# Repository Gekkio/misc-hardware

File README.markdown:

# Miscellaneous/utility/convenience hardware by Gekkio
Licensed under Creative Commons Attribution 4.0 International.

Used libraries:

* [gekkio-kicad-libs](https://github.com/Gekkio/gekkio-kicad-libs)
* [kicad-footprints](https://github.com/KiCad/kicad-footprints)
* [kicad-symbols](https://github.com/KiCad/kicad-symbols)

## ARM-JTAG-TC2050-AVR

Adapts 20-pin (2x10) 2.54 inch ARM JTAG to 10-pin IDC connector using AVR JTAG
pinout (compatible with Tag-Connect TC2050).

* PCB size: 37x51mm
* PCB thickness: any
* Layer count: 2
* Surface finish: any

## BRK-QFP-32-7x7-P0.8

Breakout board for one QFP-32 component (7x7mm body, pitch 0.8mm).

* PCB size: 39.6x52.5mm
* PCB thickness: any (1.0mm recommended)
* Layer count: 2
* Surface finish: any (ENIG recommended)

## BRK-QFP-44-10x10-P0.8

Breakout board for one QFP-44 component (10x10mm body, pitch 0.8mm).

* PCB size: 39.6x52.5mm
* PCB thickness: any (1.0mm recommended)
* Layer count: 2
* Surface finish: any (ENIG recommended)

## BRK-QFP-44-10x10-P0.8-Sharp

Breakout board for one QFP-44 component (10x10mm body, pitch 0.8mm, different
footprint used by Sharp Corporation).

* PCB size: 39.6x52.5mm
* PCB thickness: any (1.0mm recommended)
* Layer count: 2
* Surface finish: any (ENIG recommended)

## BRK-QFP-56-10x10-P0.65

Breakout board for one QFP-56 component (10x10mm body, pitch 0.65mm).

* PCB size: 45.6x57.3mm
* PCB thickness: any (1.0mm recommended)
* Layer count: 2
* Surface finish: any (ENIG recommended)

## BRK-SOT-23-3

Breakout board for two SOT-23-3 components.

* PCB size: 16.3x23.4mm
* PCB thickness: any (1.0mm recommended)
* Layer count: 2
* Surface finish: any (ENIG recommended)

## BRK-SSOP-16-4.4x5.2-P0.65

Breakout board for one SSOP-16 component (4.4x5.2mm body, pitch 0.65mm).

* PCB size: 24x32.7mm
* PCB thickness: any (1.0mm recommended)
* Layer count: 2
* Surface finish: any (ENIG recommended)

## BRK-SSOP-18-6x7.4-P0.8

Breakout board for one SSOP-18 component (6x7.4mm body, pitch 0.8mm).

* PCB size: 24x35.3mm
* PCB thickness: any (1.0mm recommended)
* Layer count: 2
* Surface finish: any (ENIG recommended)

## BRK-TSSOP-14-4.4x5-P0.65

Breakout board for one TSSOP-14 component (4.4x5mm body, pitch 0.65mm).

* PCB size: 18.9x30.2mm
* PCB thickness: any (1.0mm recommended)
* Layer count: 2
* Surface finish: any (ENIG recommended)

## BRK-TSSOP-20-4.4x6.5-P0.65

Breakout board for one TSSOP-20 component (4.4x6.5mm body, pitch 0.65mm).

* PCB size: 18.9x37.8mm
* PCB thickness: any (1.0mm recommended)
* Layer count: 2
* Surface finish: any (ENIG recommended)

## BRK-TSSOP-24-4.4x7.8-P0.65

Breakout board for one TSSOP-24 component (4.4x7.8mm body, pitch 0.65mm).

* PCB size: 18.9x42.9mm
* PCB thickness: any (1.0mm recommended)
* Layer count: 2
* Surface finish: any (ENIG recommended)

## BRK-VSSOP-8-2.4x2.1-P0.5

Breakout board for one VSSOP-8 component (2.4x2.1mm body, pitch 0.5mm).

* PCB size: 16.3x22.6mm
* PCB thickness: any (1.0mm recommended)
* Layer count: 2
* Surface finish: any (ENIG recommended)

## EV-BA33Dxx

Evaluation/breakout board for Rohm BA33Dxx linear regulators.

* PCB size: 20x29mm
* PCB thickness: any
* Layer count: 2
* Surface finish: any (ENIG recommended)

## EV-MAX-V-E64

Evaluation/breakout board for MAX V CPLDs in EQFP-64 package.

* PCB size: 70x70mm
* PCB thickness: any
* Layer count: 2
* Surface finish: any (ENIG recommended)

## PIC-ICSP-504050

Adapts 6-pin (1x6) PIC ICSP to 5-pin Molex 504050 connector.

* PCB size: 30x40mm
* PCB thickness: any
* Layer count: 2
* Surface finish: any (ENIG recommended)

## PIC-ICSP-TC2030

Adapts 6-pin (1x6) PIC ICSP to 6-pin IDC connector (compatible with Tag-Connect
TC2030).

* PCB size: 25x35mm
* PCB thickness: any
* Layer count: 2
* Surface finish: any

## TC2050-OOPS

Did you use Counter_Clockwise footprint instead of Odd_Even for TC2050 in some design? Oops!
This board fixes the pinout in this kind of scenario.

* PCB size: 27x25mm
* PCB thickness: any
* Layer count: 2
* Surface finish: any

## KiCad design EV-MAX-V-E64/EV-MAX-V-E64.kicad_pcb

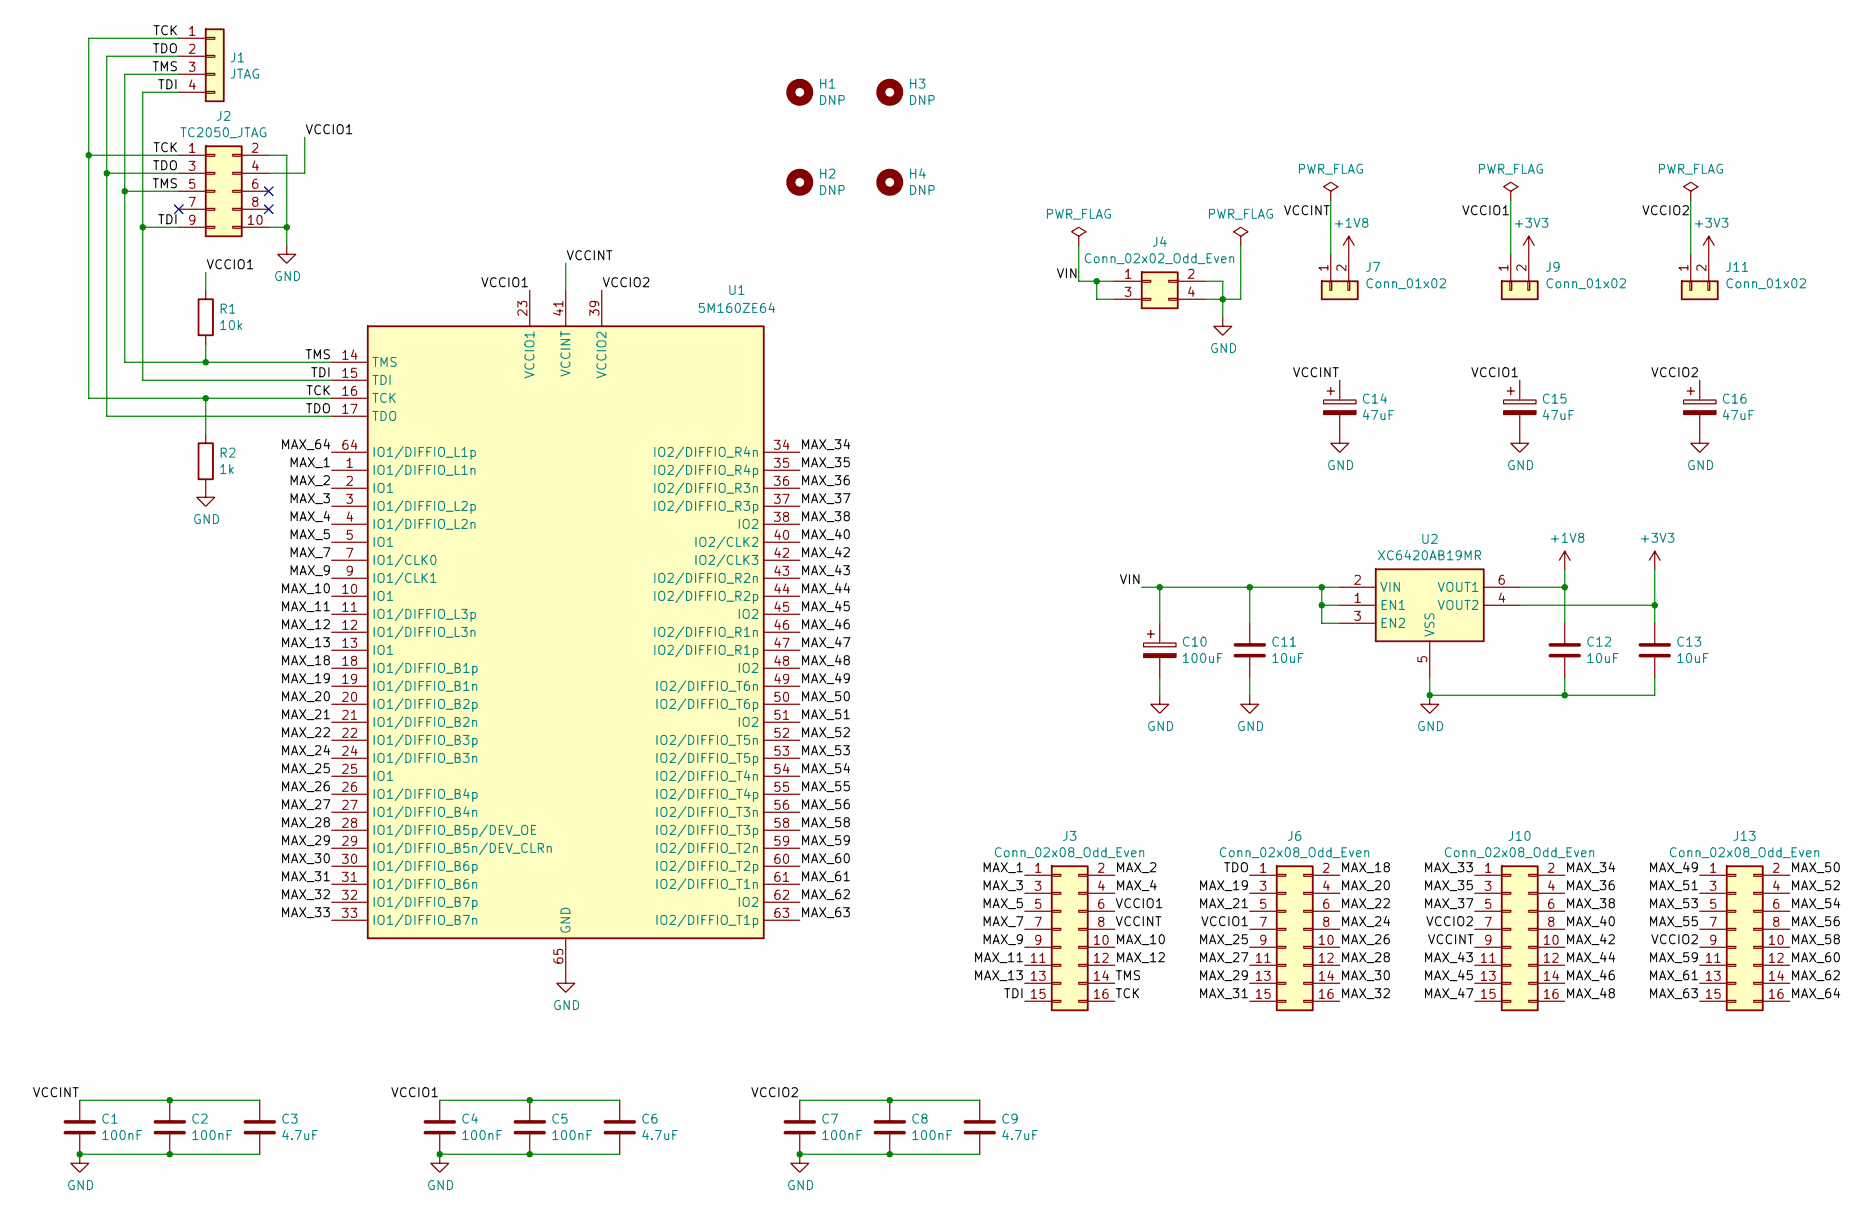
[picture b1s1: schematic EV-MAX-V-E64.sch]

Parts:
C1, C2, C4, C5, C7, C8: 100nF; C_0603_1608Metric_Pad1.05x0.95mm_HandSolder
C3, C6, C9: 4.7uF; C_0805_2012Metric_Pad1.15x1.40mm_HandSolder
C10: 100uF; CP_Elec_6.3x5.8
C11, C12, C13: 10uF; C_1206_3216Metric_Pad1.42x1.75mm_HandSolder
C14, C15, C16: 47uF; CP_Elec_5x5.8
H1, H2, H3, H4: DNP; MountingHole_3.2mm_M3
J1: JTAG; PinHeader_1x04_P2.54mm_Vertical
J2: TC2050_JTAG; Tag-Connect_TC2050-IDC-NL_2x05_P1.27mm_Vertical_with_bottom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
J3, J6, J10, J13: Conn_02x08_Odd_Even; PinHeader_2x08_P2.54mm_Vertical
J4: Conn_02x02_Odd_Even; PinHeader_2x02_P2.54mm_Vertical
J7, J9, J11: Conn_01x02; PinHeader_1x02_P2.54mm_Vertical
R1: 10k; R_0603_1608Metric_Pad1.05x0.95mm_HandSolder
R2: 1k; R_0603_1608Metric_Pad1.05x0.95mm_HandSolder
U1: 5M160ZE64; EQFP-64-1EP_7x7mm_P0.4mm_EP4.5x4.5mm
U2: XC6420AB19MR; SOT-23-6_Handsoldering

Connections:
+1V8: C12.1, J7.2, U2.6 (VOUT1)
+3V3: C13.1, J9.2, J11.2, U2.4 (VOUT2)
/MAX_1: J3.1, U1.1 (IO1/DIFFIO_L1n)
/MAX_2: J3.2, U1.2 (IO1)
/MAX_3: J3.3, U1.3 (IO1/DIFFIO_L2p)
/MAX_4: J3.4, U1.4 (IO1/DIFFIO_L2n)
/MAX_5: J3.5, U1.5 (IO1)
/MAX_7: J3.7, U1.7 (IO1/CLK0)
/MAX_9: J3.9, U1.9 (IO1/CLK1)
/MAX_10: J3.10, U1.10 (IO1)
/MAX_11: J3.11, U1.11 (IO1/DIFFIO_L3p)
/MAX_12: J3.12, U1.12 (IO1/DIFFIO_L3n)
/MAX_13: J3.13, U1.13 (IO1)
/MAX_18: J6.2, U1.18 (IO1/DIFFIO_B1p)
/MAX_19: J6.3, U1.19 (IO1/DIFFIO_B1n)
/MAX_20: J6.4, U1.20 (IO1/DIFFIO_B2p)
/MAX_21: J6.5, U1.21 (IO1/DIFFIO_B2n)
/MAX_22: J6.6, U1.22 (IO1/DIFFIO_B3p)
/MAX_24: J6.8, U1.24 (IO1/DIFFIO_B3n)
/MAX_25: J6.9, U1.25 (IO1)
/MAX_26: J6.10, U1.26 (IO1/DIFFIO_B4p)
/MAX_27: J6.11, U1.27 (IO1/DIFFIO_B4n)
/MAX_28: J6.12, U1.28 (IO1/DIFFIO_B5p/DEV_OE)
/MAX_29: J6.13, U1.29 (IO1/DIFFIO_B5n/DEV_CLRn)
/MAX_30: J6.14, U1.30 (IO1/DIFFIO_B6p)
/MAX_31: J6.15, U1.31 (IO1/DIFFIO_B6n)
/MAX_32: J6.16, U1.32 (IO1/DIFFIO_B7p)
/MAX_33: J10.1, U1.33 (IO1/DIFFIO_B7n)
/MAX_34: J10.2, U1.34 (IO2/DIFFIO_R4n)
/MAX_35: J10.3, U1.35 (IO2/DIFFIO_R4p)
/MAX_36: J10.4, U1.36 (IO2/DIFFIO_R3n)
/MAX_37: J10.5, U1.37 (IO2/DIFFIO_R3p)
/MAX_38: J10.6, U1.38 (IO2)
/MAX_40: J10.8, U1.40 (IO2/CLK2)
/MAX_42: J10.10, U1.42 (IO2/CLK3)
/MAX_43: J10.11, U1.43 (IO2/DIFFIO_R2n)
/MAX_44: J10.12, U1.44 (IO2/DIFFIO_R2p)
/MAX_45: J10.13, U1.45 (IO2)
/MAX_46: J10.14, U1.46 (IO2/DIFFIO_R1n)
/MAX_47: J10.15, U1.47 (IO2/DIFFIO_R1p)
/MAX_48: J10.16, U1.48 (IO2)
/MAX_49: J13.1, U1.49 (IO2/DIFFIO_T6n)
/MAX_50: J13.2, U1.50 (IO2/DIFFIO_T6p)
/MAX_51: J13.3, U1.51 (IO2)
/MAX_52: J13.4, U1.52 (IO2/DIFFIO_T5n)
/MAX_53: J13.5, U1.53 (IO2/DIFFIO_T5p)
/MAX_54: J13.6, U1.54 (IO2/DIFFIO_T4n)
/MAX_55: J13.7, U1.55 (IO2/DIFFIO_T4p)
/MAX_56: J13.8, U1.56 (IO2/DIFFIO_T3n)
/MAX_58: J13.10, U1.58 (IO2/DIFFIO_T3p)
/MAX_59: J13.11, U1.59 (IO2/DIFFIO_T2n)
/MAX_60: J13.12, U1.60 (IO2/DIFFIO_T2p)
/MAX_61: J13.13, U1.61 (IO2/DIFFIO_T1n)
/MAX_62: J13.14, U1.62 (IO2)
/MAX_63: J13.15, U1.63 (IO2/DIFFIO_T1p)
/MAX_64: J13.16, U1.64 (IO1/DIFFIO_L1p)
/TCK: J1.1, J2.1, J3.16, R2.1, U1.16 (TCK)
/TDI: J1.4, J2.9, J3.15, U1.15 (TDI)
/TDO: J1.2, J2.3, J6.1, U1.17 (TDO)
/TMS: J1.3, J2.5, J3.14, R1.2, U1.14 (TMS)
/VCCINT: C1.1, C2.1, C3.1, C14.1, J3.8, J7.1, J10.9, U1.8 (VCCINT), U1.41 (VCCINT)
/VCCIO1: C4.1, C5.1, C6.1, C15.1, J2.4, J3.6, J6.7, J9.1, R1.1, U1.6 (VCCIO1), U1.23 (VCCIO1)
/VCCIO2: C7.1, C8.1, C9.1, C16.1, J10.7, J11.1, J13.9, U1.39 (VCCIO2), U1.57 (VCCIO2)
/VIN: C10.1, C11.1, J4.1, J4.3, U2.1 (EN1), U2.2 (VIN), U2.3 (EN2)
GND: C1.2, C2.2, C3.2, C4.2, C5.2, C6.2, C7.2, C8.2, C9.2, C10.2, C11.2, C12.2, C13.2, C14.2, C15.2, C16.2, J2.2, J2.10, J4.2, J4.4, R2.2, U1.65 (GND), U2.5 (VSS)

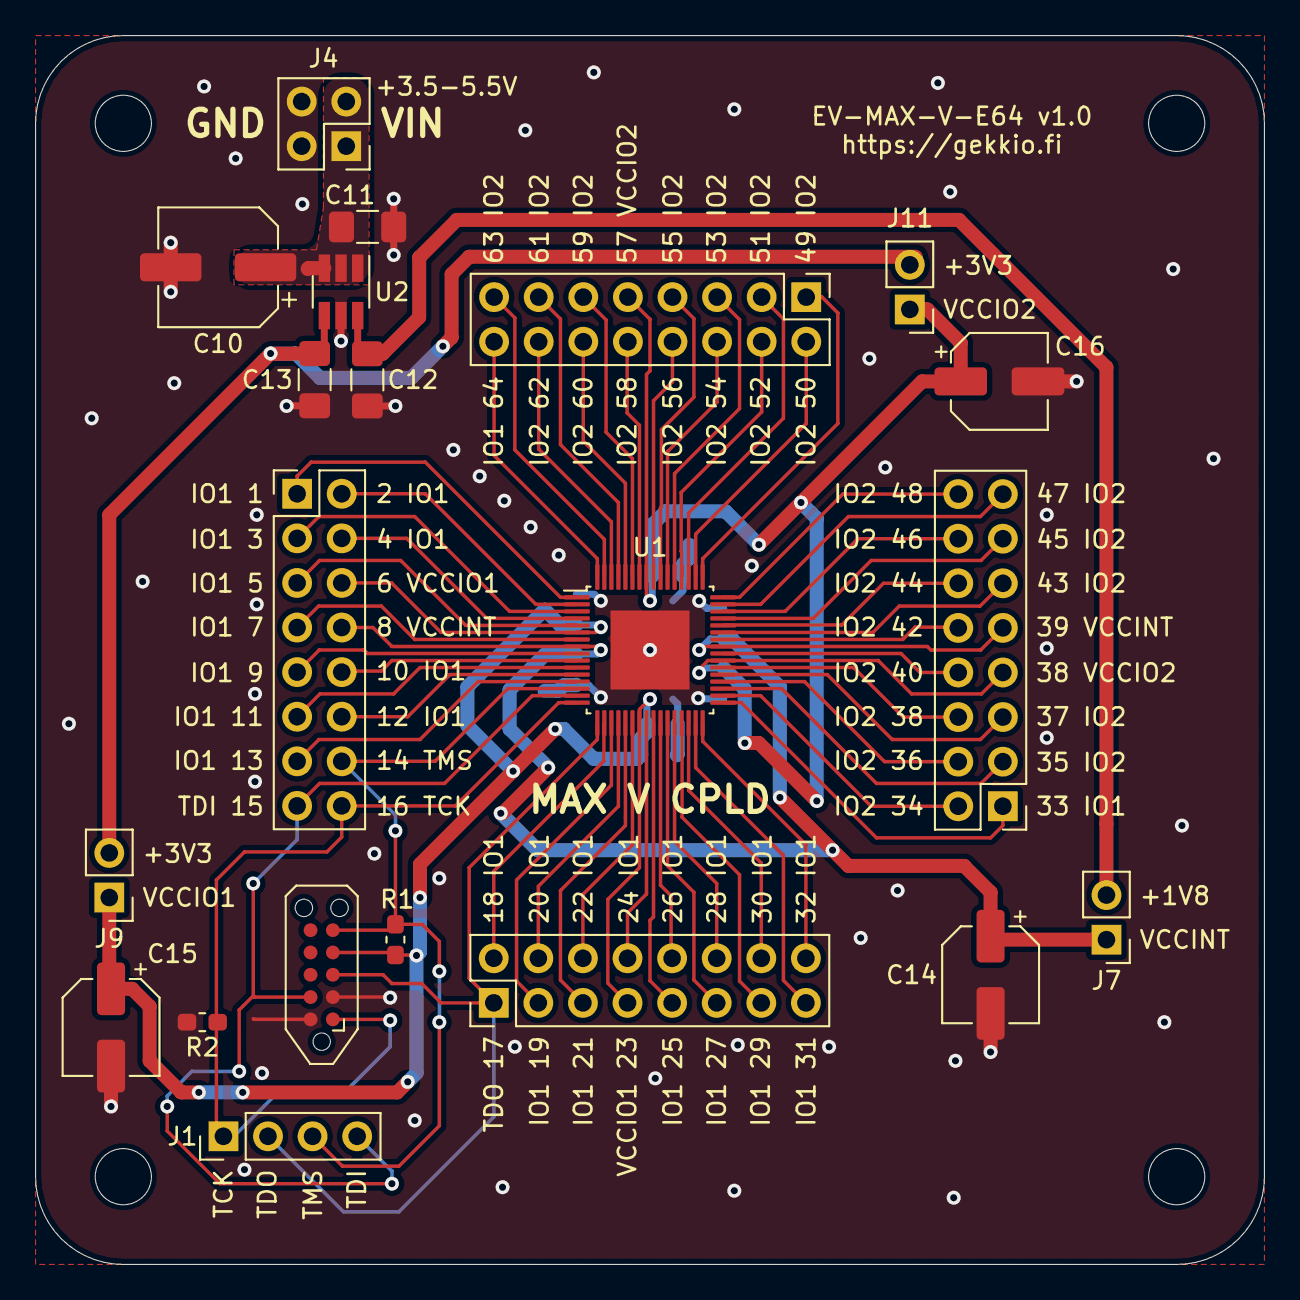
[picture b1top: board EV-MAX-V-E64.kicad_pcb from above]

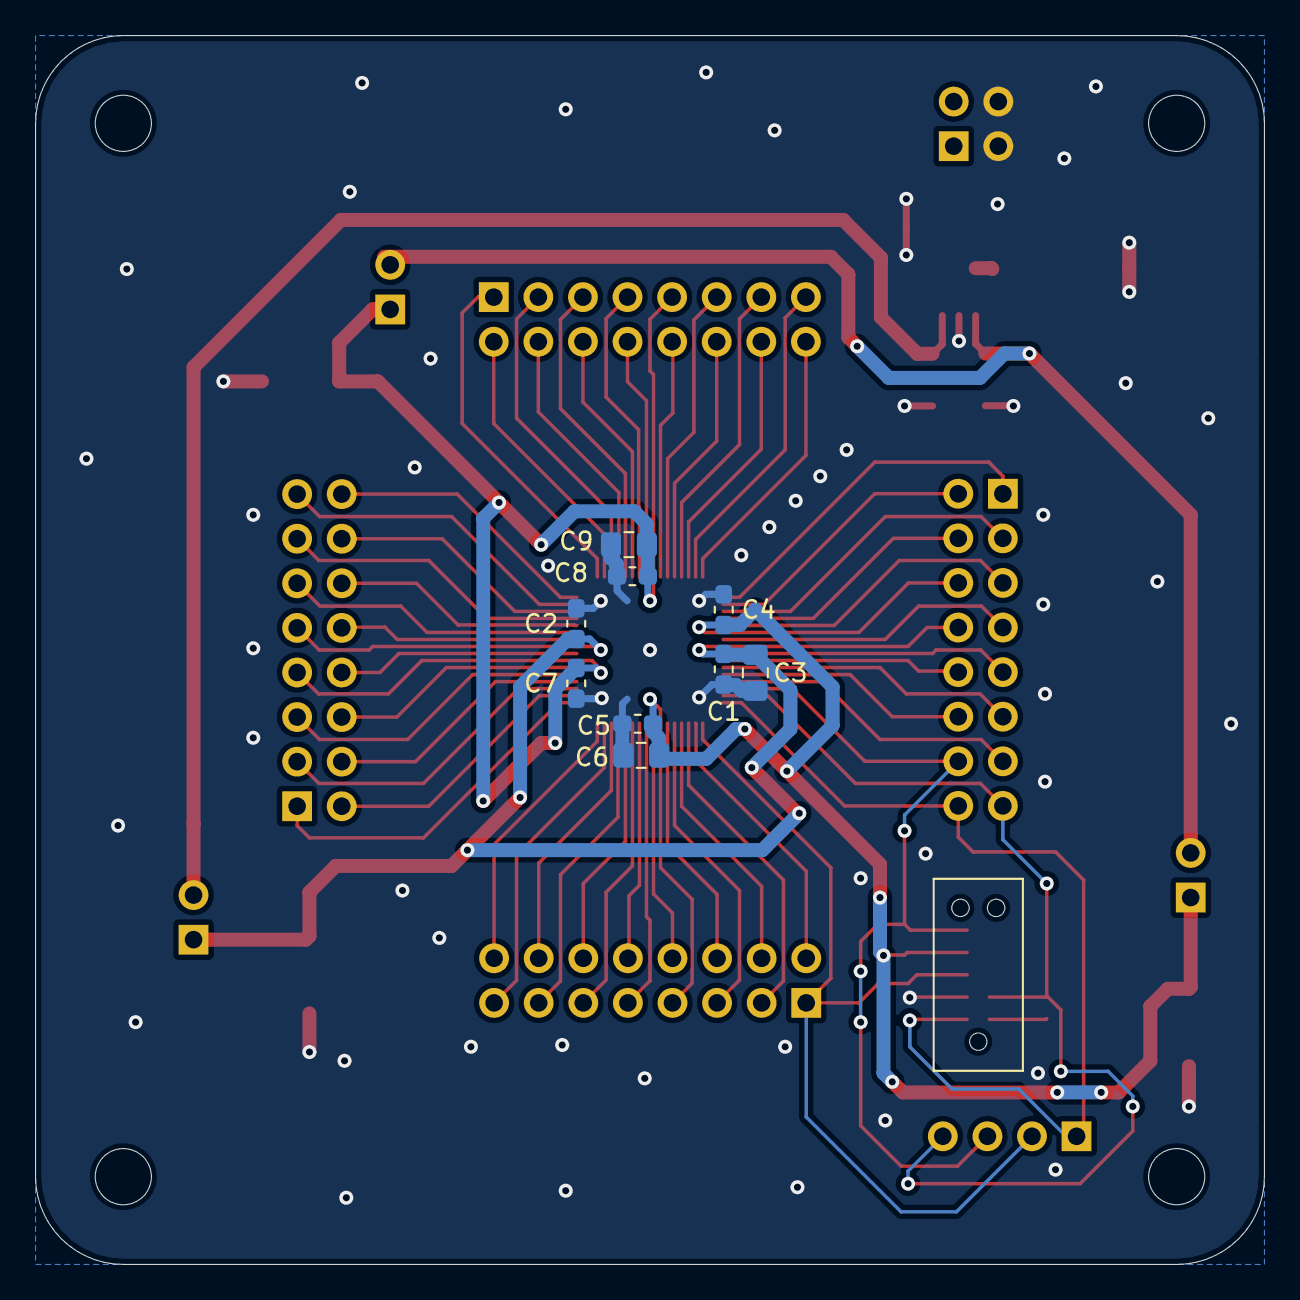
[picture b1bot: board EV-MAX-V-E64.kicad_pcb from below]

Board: 2 copper layers, 70.0 x 70.0 mm, 34 parts (9 on the bottom side), 65 nets.

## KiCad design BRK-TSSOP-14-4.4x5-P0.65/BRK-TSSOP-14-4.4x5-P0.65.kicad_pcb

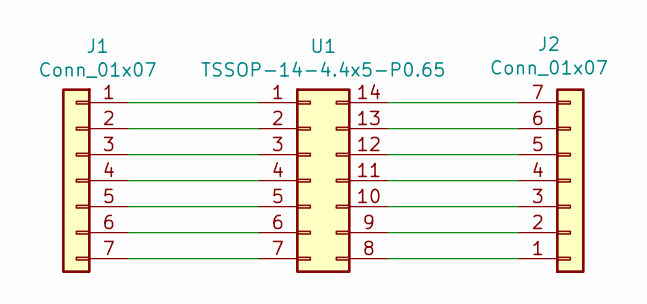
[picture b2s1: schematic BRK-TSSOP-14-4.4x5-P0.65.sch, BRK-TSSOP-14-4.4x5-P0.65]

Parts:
J1, J2: Conn_01x07; PinHeader_1x07_P2.54mm_Vertical
U1: TSSOP-14-4.4x5-P0.65; TSSOP-14_4.4x5mm_P0.65mm

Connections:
unnamed: J1.1, U1.1
unnamed: J1.2, U1.2
unnamed: J1.3, U1.3
unnamed: J1.4, U1.4
unnamed: J1.5, U1.5
unnamed: J1.6, U1.6
unnamed: J1.7, U1.7
unnamed: J2.1, U1.8
unnamed: J2.2, U1.9
unnamed: J2.3, U1.10
unnamed: J2.4, U1.11
unnamed: J2.5, U1.12
unnamed: J2.6, U1.13
unnamed: J2.7, U1.14

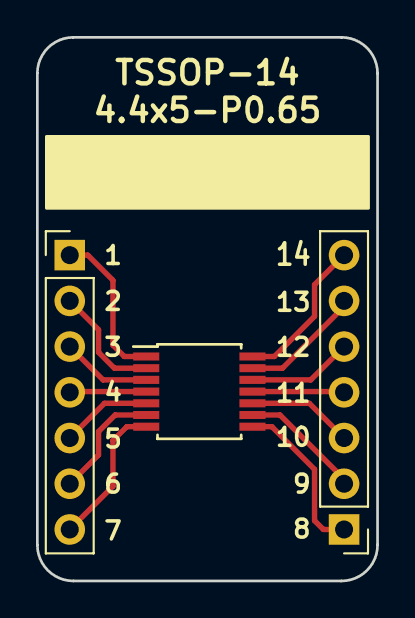
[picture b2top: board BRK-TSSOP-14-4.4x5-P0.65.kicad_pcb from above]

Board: 2 copper layers, 18.9 x 30.2 mm, 3 parts (0 on the bottom side), 14 nets.

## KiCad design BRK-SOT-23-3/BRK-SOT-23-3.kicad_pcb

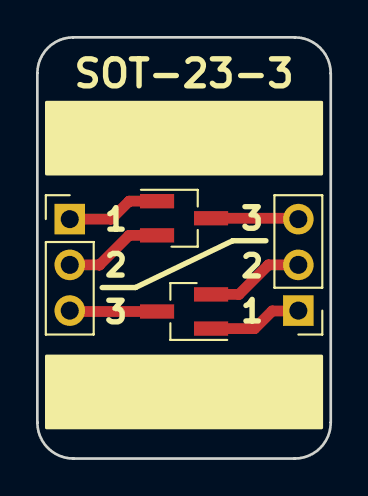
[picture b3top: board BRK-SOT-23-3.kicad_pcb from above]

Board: 2 copper layers, 16.3 x 23.4 mm, 4 parts (0 on the bottom side), 6 nets.

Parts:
J1, J2: Conn_01x03; PinHeader_1x03_P2.54mm_Vertical
U1, U2: SOT-23-3; SOT-23_Handsoldering

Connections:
unnamed: J1.1, U1.1
unnamed: J1.2, U1.2
unnamed: J1.3, U2.3
unnamed: J2.1, U2.1
unnamed: J2.2, U2.2
unnamed: J2.3, U1.3

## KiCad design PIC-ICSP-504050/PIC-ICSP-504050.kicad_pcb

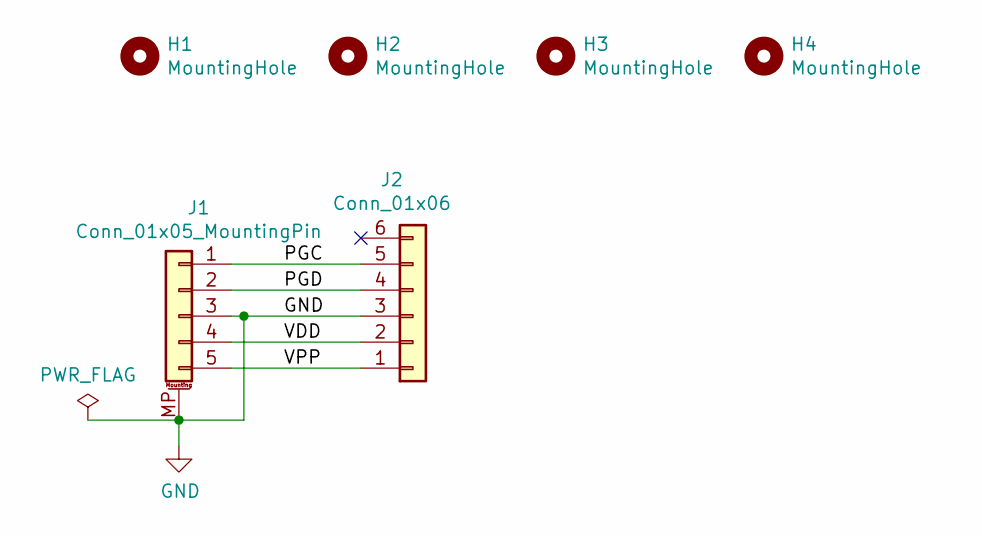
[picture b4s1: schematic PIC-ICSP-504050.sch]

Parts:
H1, H2, H3, H4: MountingHole; MountingHole_3.2mm_M3
J1: Conn_01x05_MountingPin; Molex_Pico-Lock_504050-0591_1x05-1MP_P1.50mm_Horizontal
J2: Conn_01x06; PinHeader_1x06_P2.54mm_Vertical

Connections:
/PGC: J1.1, J2.5
/PGD: J1.2, J2.4
/VDD: J1.4, J2.2
/VPP: J1.5, J2.1
GND: J1.3, J1.MP (MountPin), J2.3

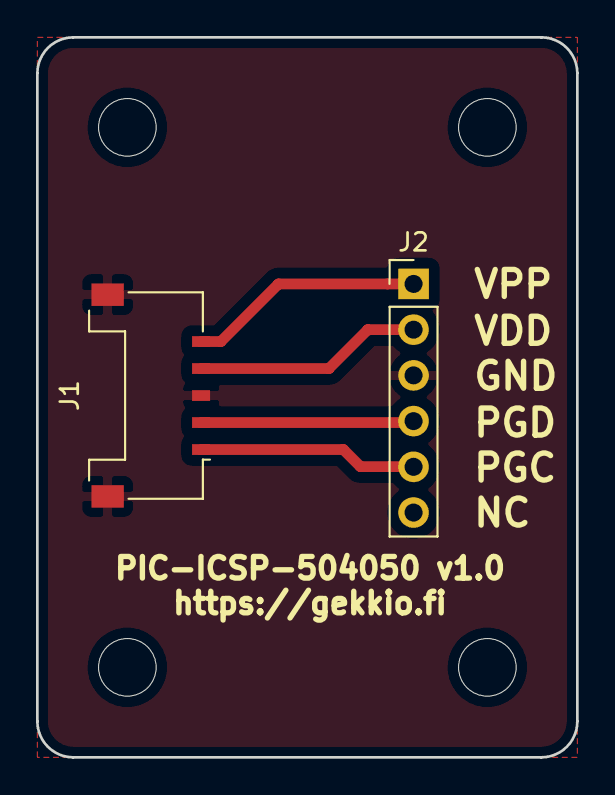
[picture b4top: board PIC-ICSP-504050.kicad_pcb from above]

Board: 2 copper layers, 30.0 x 40.0 mm, 6 parts (0 on the bottom side), 5 nets.

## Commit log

2018-11-26 Minor updates
2018-11-26 Add descriptions
2018-11-26 Add 3D renderings
2018-12-01 BRK-SOT-23-6, BSK-MSOP-8-3x3-P0.65, BRK-VSSOP-8-2.4x2.1-P0.5
2019-08-10 Update several breakout boards
    * Reduce distance from edge to pin header
    * Enlarge silk screen area
2019-08-10 Remove unused git submodule
2019-08-10 Add BRK-SSOP-16-4.4x5.2-P0.65
2019-08-10 Add BRK-SSOP-18-6x7.4-P0.8
2020-02-24 More breakout boards
2020-02-24 Use shallow git submodules
2020-02-24 Revert "Use shallow git submodules"
    This reverts commit 33df837b4b37f2490ae75f0c3fc7e02f237eb51b.
2020-02-24 Clean old backup files
2020-02-24 Use a different submodule setup
2020-02-24 Rename third-party -> external
2020-03-01 Add more designs
2020-03-01 Update 3d images
2020-05-16 Add TC2050-OOPS
2020-05-16 Add EV-BA33Dxx
2020-05-16 Oops
2020-05-16 Remove old BUS-BLASTER-AVR-* boards
2020-05-16 Set solder mask min width to 0, regenerate gerbers
2020-07-16 Add EV-MAX-V-E64 v1.0
2020-11-06 Add new semi-automatically generated breakout boards
